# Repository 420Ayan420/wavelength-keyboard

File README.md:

# wavelength-keyboard
A custom ortholinear bluetooth mechanical keyboard with a left-sided numpad. Supports low-profile Kalih Choc(olate) switches and has additional dev-connectors for accessing the MCU for other projects such as the [analog gauge based task manager](https://github.com/420Ayan420/analog-task-manager), etc.

# keyboard layout
I am using ortholinear as it is more comfortable and natural to type on, I am also using a left-sided numpad making mouse positionining more comfortable. Using [KLE](http://www.keyboard-layout-editor.com/) (keyboard layout editor) you can open the `layout.json` file to edit/view it to your needs.

# hardware
I have chosen the nrf52840 MCU as it has abundant GPIO pins for all the rows and columns in my switch matrix, it also has built-in bluetooth support. Regarding the I have also chosen the [Choc v1](https://chosfox.com/products/kailh-chocs) switches as they are low profile and have hot-swap sockets.

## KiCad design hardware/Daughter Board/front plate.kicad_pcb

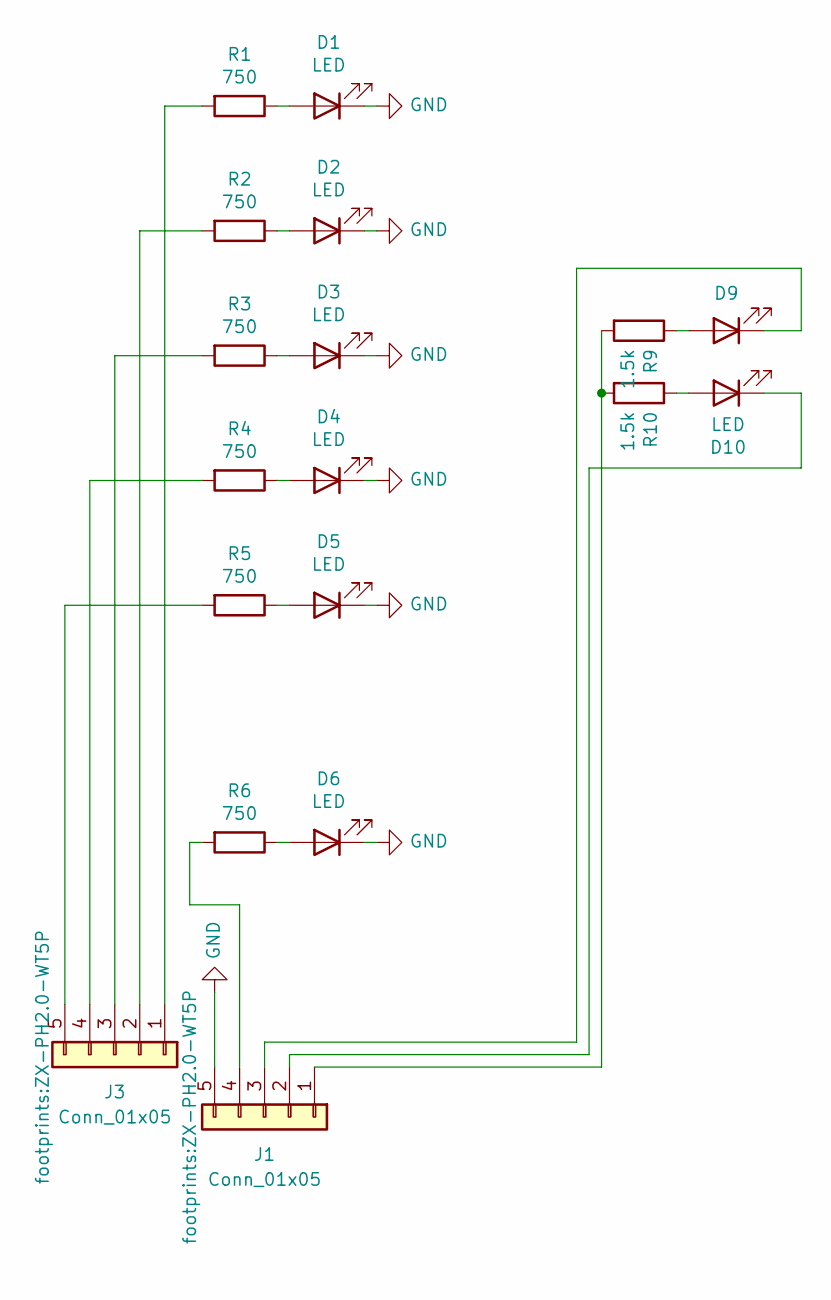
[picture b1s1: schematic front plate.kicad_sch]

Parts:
D1, D2, D3, D4, D5, D6: LED; LED_1206_3216Metric
D9, D10: LED; LED_0603_1608Metric
J1, J3: Conn_01x05; ZX-PH2.0-WT5P
R1, R2, R3, R4, R5, R6: 750; R_0603_1608Metric
R9, R10: 1.5k; R_0603_1608Metric

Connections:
GND: D1.1 (K), D2.1 (K), D3.1 (K), D4.1 (K), D5.1 (K), D6.1 (K), J1.5
unnamed: D1.2 (A), R1.1
unnamed: D2.2 (A), R2.1
unnamed: D3.2 (A), R3.1
unnamed: D4.2 (A), R4.1
unnamed: D5.2 (A), R5.1
unnamed: D6.2 (A), R6.1
unnamed: D9.2 (A), R9.1
unnamed: D9.1 (K), J1.3
unnamed: D10.2 (A), R10.1
unnamed: D10.1 (K), J1.2
unnamed: J1.1, R9.2, R10.2
unnamed: J1.4, R6.2
unnamed: J3.1, R1.2
unnamed: J3.2, R2.2
unnamed: J3.3, R3.2
unnamed: J3.4, R4.2
unnamed: J3.5, R5.2

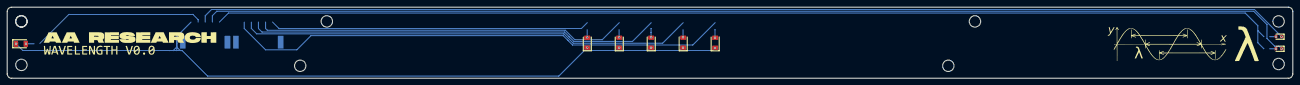
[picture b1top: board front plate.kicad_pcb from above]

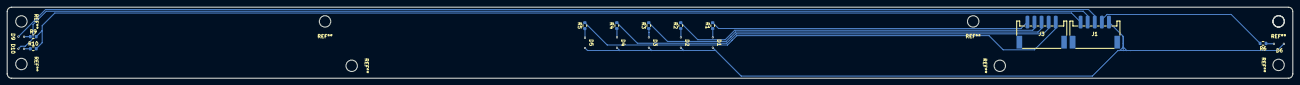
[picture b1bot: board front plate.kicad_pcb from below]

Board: 2 copper layers, 362.0 x 20.0 mm, 18 parts (10 on the bottom side), 18 nets.

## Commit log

2025-03-07 add all files
